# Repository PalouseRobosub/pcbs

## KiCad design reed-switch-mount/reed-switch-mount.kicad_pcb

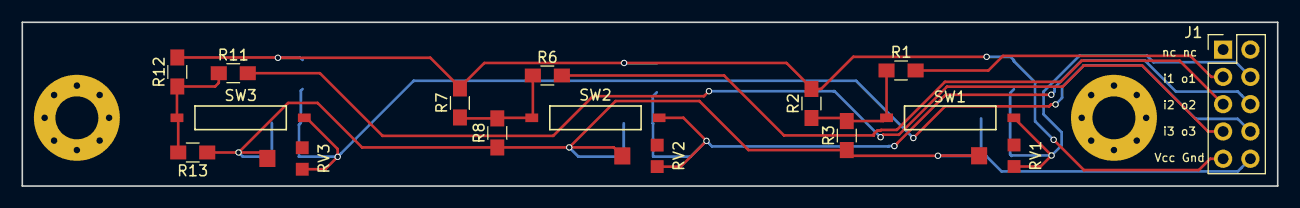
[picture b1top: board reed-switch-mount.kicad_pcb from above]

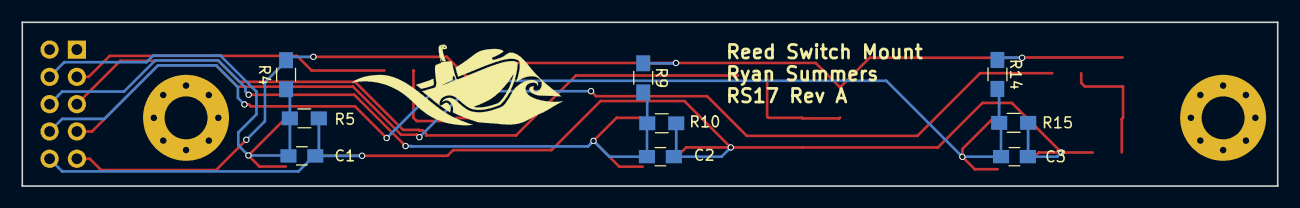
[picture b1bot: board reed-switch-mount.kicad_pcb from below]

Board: 2 copper layers, 116.8 x 15.2 mm, 25 parts (9 on the bottom side), 11 nets.

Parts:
C1, C2, C3: C; C_0805_HandSoldering
J1: CONN_02X05; Pin_Header_Straight_2x05_Pitch2.54mm
R1, R2, R3, R4, R5, R6, R7, R8, R9, R10, R11, R12, R13, R14, R15: R; R_0805_HandSoldering
RV1, RV2, RV3: POT; TC33X-2
SW1, SW2, SW3: SW_DIP_x01; MK17-reed-switch

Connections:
/Vcommon: J1.9, R2.2, R4.1, R7.2, R9.1, R12.2, R14.1
/Vin1: J1.3, R1.2
/Vin2: J1.5, R6.2
/Vin3: J1.7, R11.2
/Vout1: C1.1, J1.4, R4.2, R5.1, RV1.1, SW1.2
/Vout2: C2.1, J1.6, R9.2, R10.1, RV2.1, SW2.2
/Vout3: C3.1, J1.8, R14.2, R15.1, RV3.1, SW3.2
GND: C1.2, C2.2, C3.2, J1.10, R3.1, R5.2, R8.1, R10.2, R13.1, R15.2, RV1.2, RV2.2, RV3.2
unnamed: R1.1, R2.1, R3.2, SW1.1
unnamed: R6.1, R7.1, R8.2, SW2.1
unnamed: R11.1, R12.1, R13.2, SW3.1

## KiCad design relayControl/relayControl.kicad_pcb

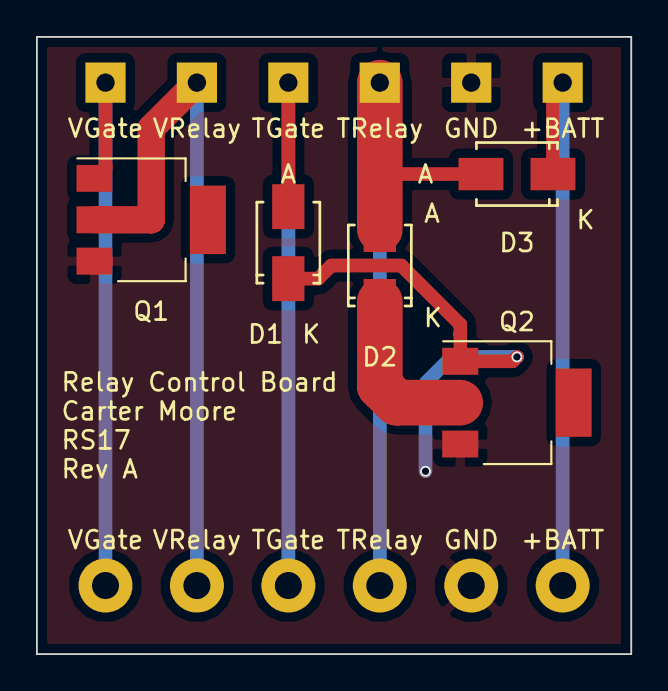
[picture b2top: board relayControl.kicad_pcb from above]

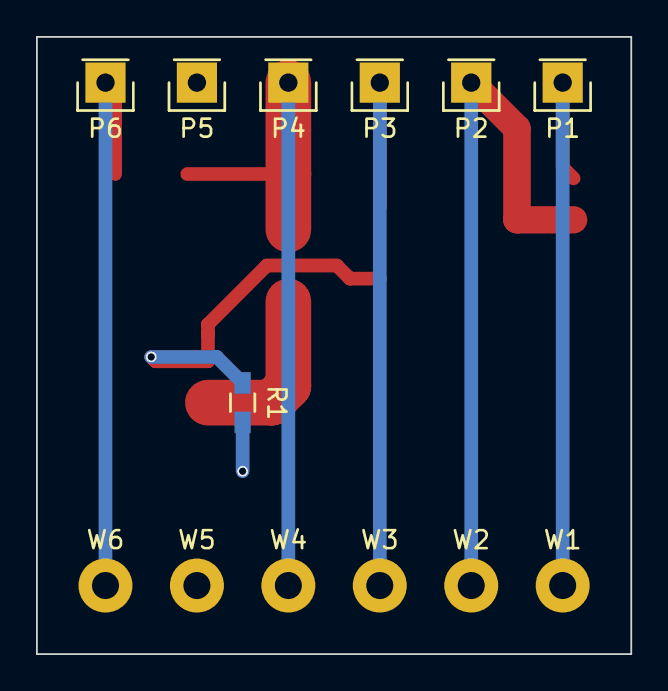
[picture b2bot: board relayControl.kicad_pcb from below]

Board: 2 copper layers, 33.0 x 34.3 mm, 18 parts (13 on the bottom side), 8 nets.

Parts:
D1, D2, D3: D; SMA_Standard
P1, P2, P3, P4, P5, P6: CONN_01X01; Pin_Header_Straight_1x01
Q1, Q2: Q_NMOS_GDS; SOT-223
R1: 1.5K; R_0603_HandSoldering
W1, W2, W3, W4, W5, W6: TEST_1P; Measurement_Point_Round-TH_Big

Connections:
+BATT: D3.1, P6.1, W6.1
/TGate: D1.2, P3.1, W3.1
/TRelay: D2.2, D3.2, P4.1, W4.1
/VGate: P1.1, Q1.1, W1.1
/VRelay: P2.1, Q1.2, W2.1
GND: P5.1, Q1.3, Q2.3, R1.2, W5.1
unnamed: D1.1, Q2.1, R1.1
unnamed: D2.1, Q2.2

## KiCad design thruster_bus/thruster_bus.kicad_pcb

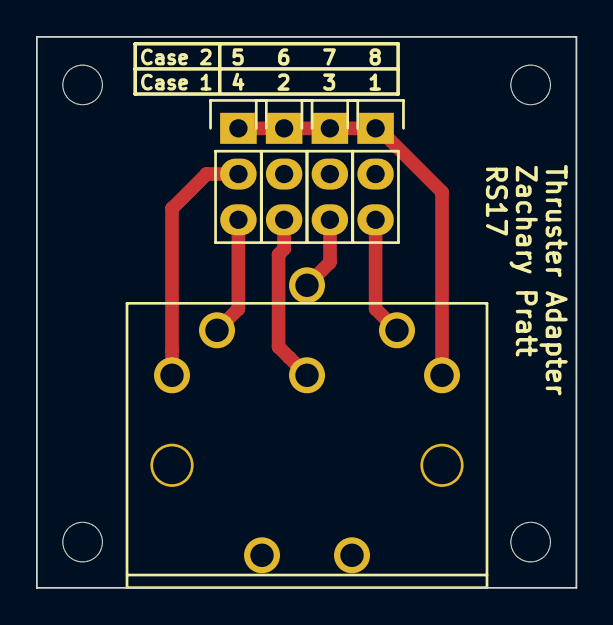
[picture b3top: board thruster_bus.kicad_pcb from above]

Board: 2 copper layers, 30.0 x 30.6 mm, 5 parts (0 on the bottom side), 6 nets.

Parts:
P1, P2, P3, P5: CONN_01X03; Pin_Header_Straight_1x03
P4: CONN_01X06; cui-6-board-f

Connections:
/2: P2.3, P4.2
/4: P4.4, P5.3
/5: P1.3, P4.5
/6: P3.3, P4.6
/ESC5V: P1.2, P4.3
GND: P1.1, P2.1, P3.1, P4.1, P5.1

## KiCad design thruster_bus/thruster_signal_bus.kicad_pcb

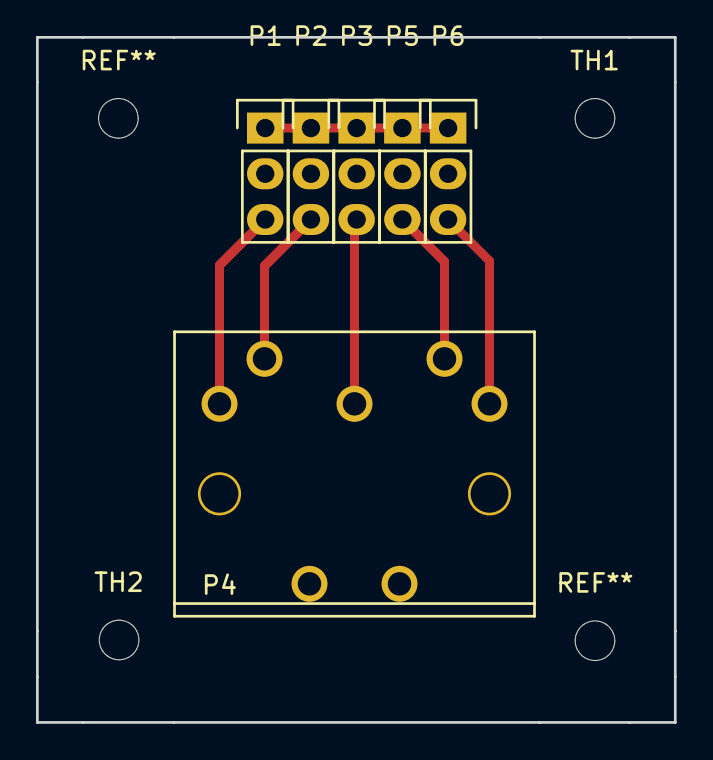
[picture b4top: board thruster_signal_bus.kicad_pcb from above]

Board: 2 copper layers, 35.4 x 38.1 mm, 8 parts (0 on the bottom side), 6 nets.

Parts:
P1, P2, P3, P5, P6: CONN_01X03; Pin_Header_Straight_1x03
P4: CONN_01X05; cui-5-board-f
TH1, TH2: MountingHole_2.2mm_M2

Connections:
/1: P4.1, P6.3
/2: P3.3, P4.2
/3: P1.3, P4.3
/4: P4.4, P5.3
/5: P2.3, P4.5
GND: P1.1, P2.1, P3.1, P5.1, P6.1
